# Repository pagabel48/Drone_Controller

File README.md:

# Drone Controller

The control board is based around an STM32f401 MCU. For power regulation a buck converter is used to generate steady 3.3v from a 4s LiPO Battery or USB 5v line. When powered over battery, the highside power latch allows the board to be toggled on or off.

To allow for closed loop control a BMP280 barometer and an ICM42670P IMU are connected over I2C, and PWM is used to communicate with the motor ESCs and controller receiver. Programming is done over USB, and pins are exposed for UART, I2C, and SWD protocols for extensibility.

Four layers were used to make routing easier and improve signal integrity.

## Routing

## Schematic

# Code

State estimation is achieved with two Kalman filters (attitude and altitude), and PID controllers are used in combination with a mixer to get final motor throttle values.

Custom drivers were written to interface with the sensors, and a matrix math library was written using c++ operator overloading - this allows for readable state space control code. The IMU driver reads when triggered by a pin interupt, and the barometer driver uses polling.

A testing routine was written which can be run instead of the main drone loop - it runs unit tests for the code, then tests operation of the sensors, motors, Kalman filters, and status light.

The firmware automatically turns the drone off when the battery voltage drops below a safe level.

Controller Code is Contained in Firmare/Core/

## Code Structure

# Frame

The frame was designed in fusion 360 and was 3d printed using PETG plastic. Care was taken to maximize rigidity whilst minimizing weight.

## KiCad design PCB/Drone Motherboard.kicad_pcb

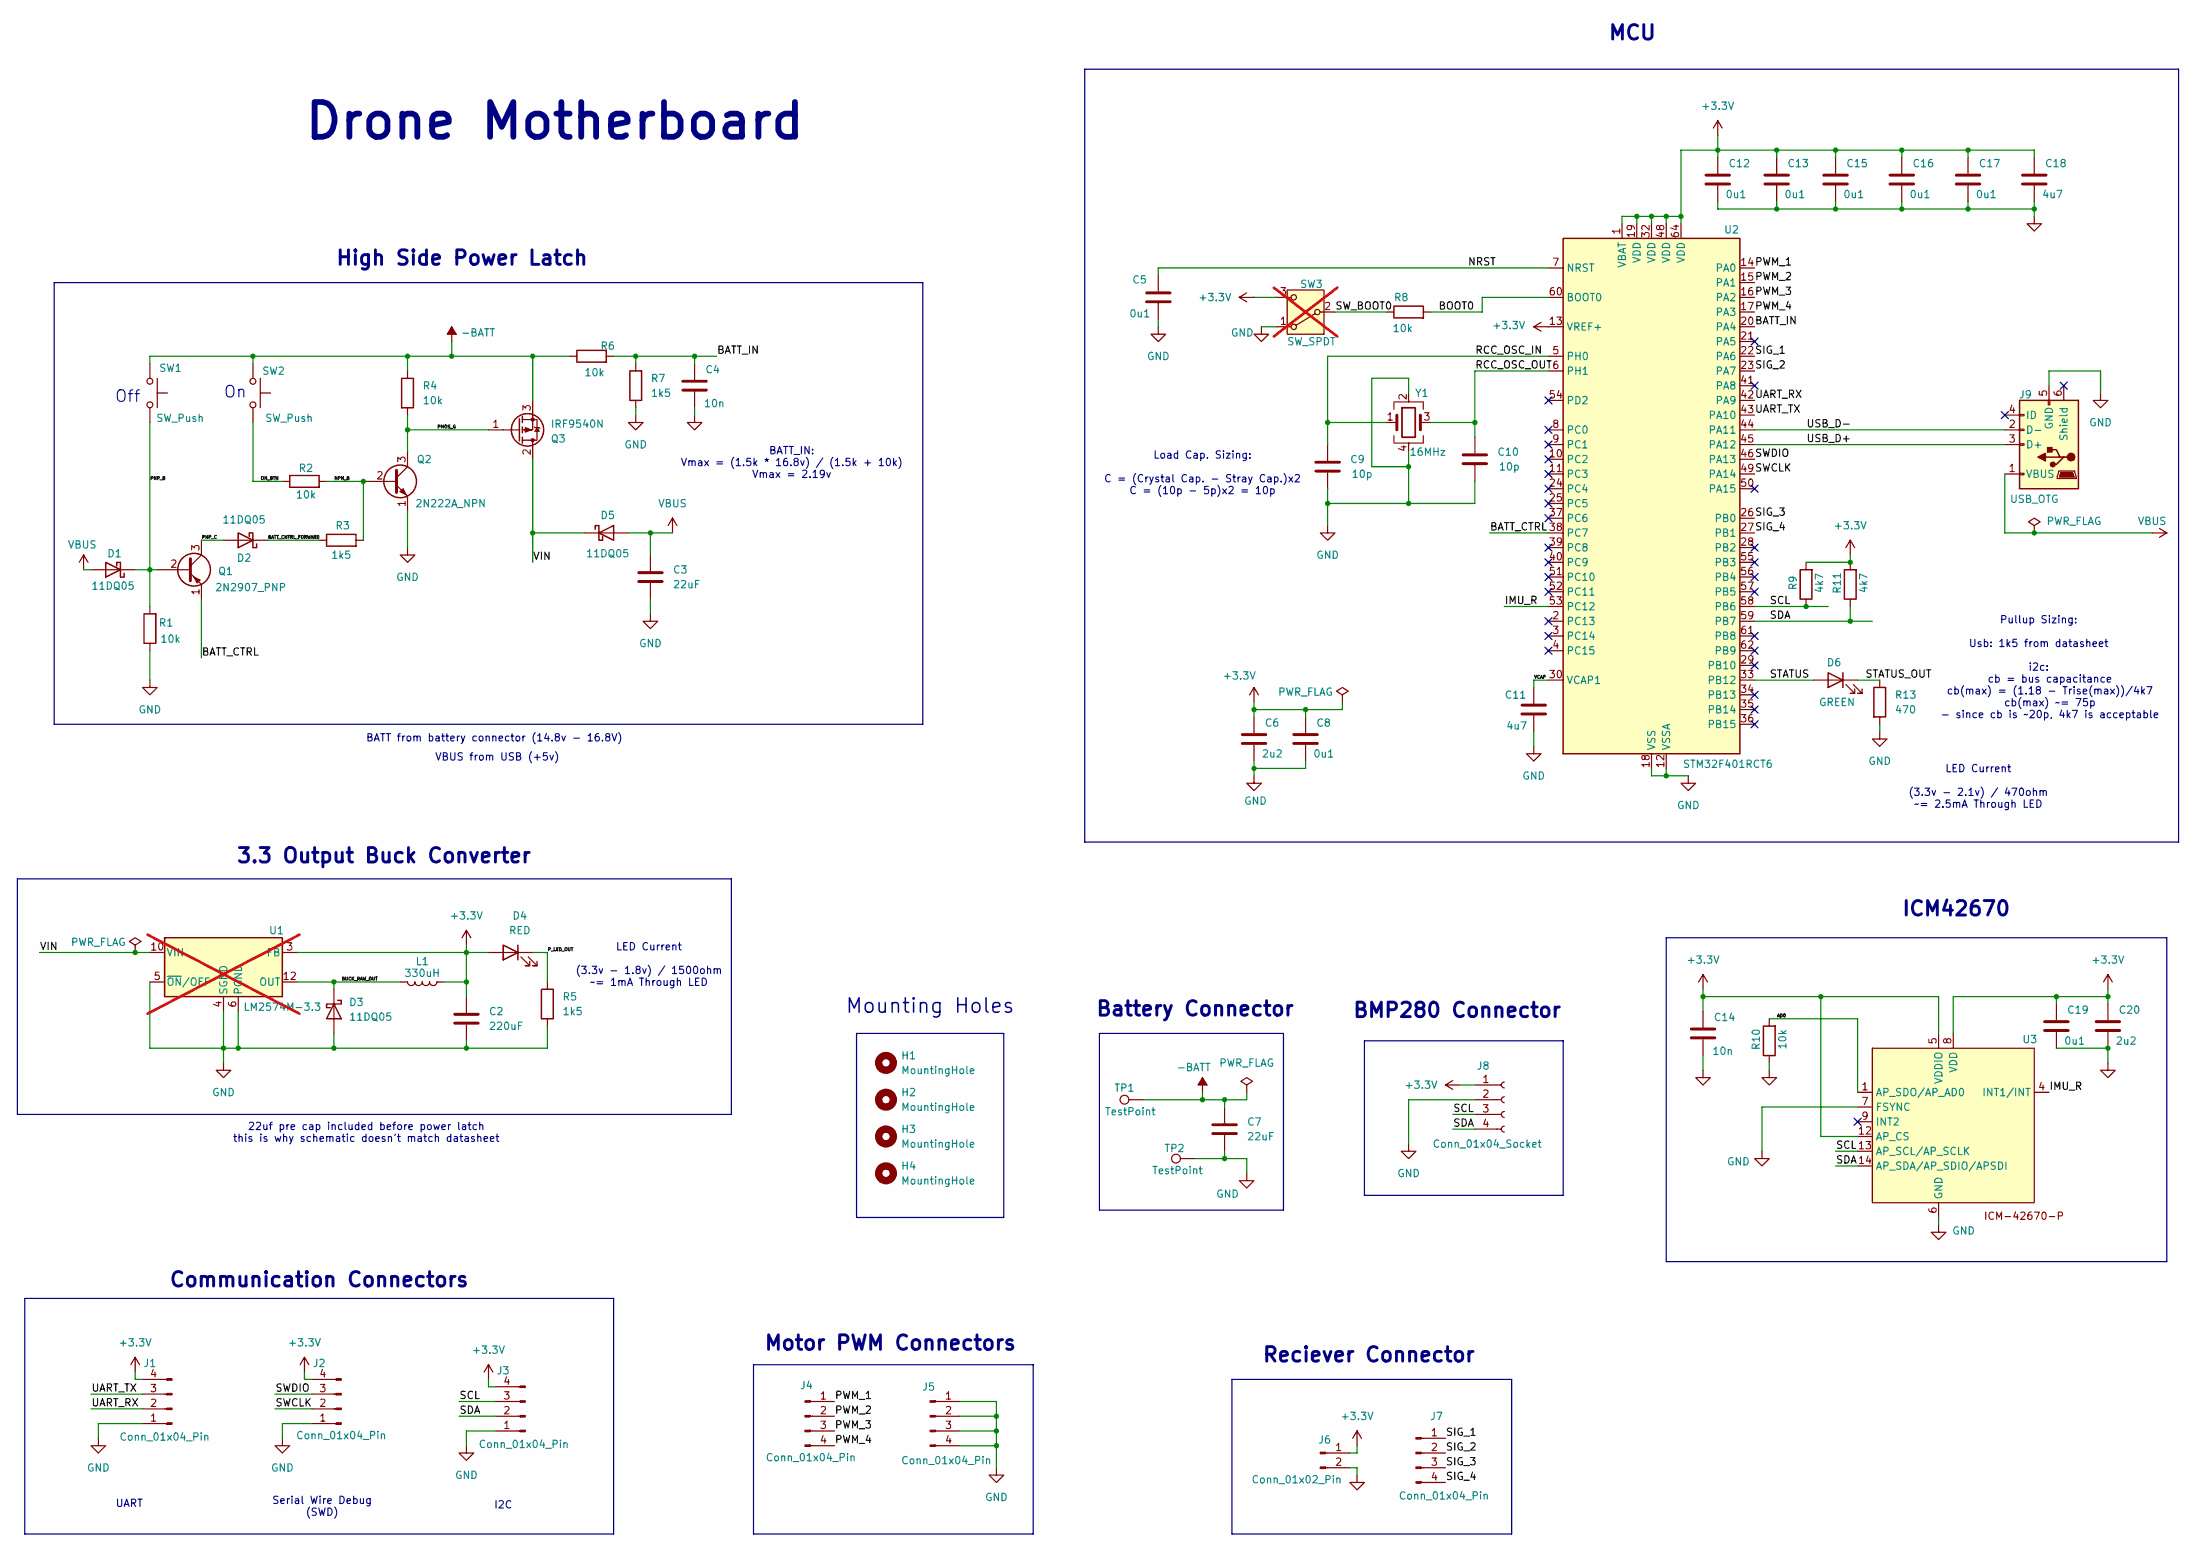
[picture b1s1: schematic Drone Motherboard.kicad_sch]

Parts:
C2: 220uF; C_Radial_D6.3mm_H11.0mm_P2.50mm
C3, C7: 22uF; C_Radial_D5.0mm_H5.0mm_P2.00mm
C4, C14: 10n; C_0402_1005Metric; LCSC C60133
C5, C8, C12, C13, C15, C16, C17, C19: 0u1; C_0402_1005Metric; LCSC C60474
C6, C20: 2u2; C_0402_1005Metric; LCSC C170151
C9, C10: 10p; C_0402_1005Metric; LCSC C106199
C11, C18: 4u7; C_0402_1005Metric; LCSC C23733
D1, D2, D3, D5: 11DQ05; D_DO-41_SOD81_P7.62mm_Horizontal
D4: RED; LED_D5.0mm_Clear
D6: GREEN; LED_D5.0mm_Clear
H1, H2, H3, H4: MountingHole; MountingHole_3.2mm_M3_Pad
J1, J2, J3, J4, J5, J7: Conn_01x04_Pin; PinHeader_1x04_P2.54mm_Vertical
J6: Conn_01x02_Pin; PinHeader_1x02_P2.54mm_Vertical
J8: Conn_01x04_Socket; PinHeader_1x04_P2.54mm_Vertical
J9: USB_OTG; USB_Micro-B_Amphenol_10118193-0001LF_Horizontal; LCSC C132563
L1: 330uH; L_Axial_L5.3mm_D2.2mm_P7.62mm_Horizontal_Vishay_IM-1
Q1: 2N2907_PNP; TO-92
Q2: 2N222A_NPN; TO-92
Q3: IRF9540N; TO-220-3_Vertical
R1, R2, R4, R6, R8, R10: 10k; R_0402_1005Metric; LCSC C25744
R3, R5, R7: 1k5; R_0402_1005Metric; LCSC C25867
R9, R11: 4k7; R_0402_1005Metric; LCSC C105871
R13: 470; R_0402_1005Metric; LCSC C25117
SW1, SW2: SW_Push; SW_PUSH_6mm
SW3: SW_SPDT; CUS-12TB_NDC; not fitted
TP1, TP2: TestPoint; TestPoint_Pad_4.0x4.0mm
U1: LM2574M-3.3; SOIC-14W_7.5x9mm_P1.27mm; not fitted
U2: STM32F401RCT6; LQFP-64_10x10mm_P0.5mm; LCSC C74524
U3: LGA-14_3x2.5mm_P0.5mm_LayoutBorder3x4y; LCSC C3288646
Y1: 16MHz; Crystal_SMD_3225-4Pin_3.2x2.5mm; LCSC C41383241

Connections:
+3.3V: C2.1, C6.1, C8.1, C12.1, C13.1, C14.1, C15.1, C16.1, C17.1, C18.1, C19.1, C20.1, D4.2 (A), J1.4, J2.4, J3.4, J6.1, J8.1, L1.1, R9.2, R11.2, SW3.3 (C), U1.3 (FB), U2.1 (VBAT), U2.13 (VREF+), U2.19 (VDD), U2.32 (VDD), U2.48 (VDD), U2.64 (VDD), U3.5 (VDDIO), U3.8 (VDD), U3.12 (AP_CS)
-BATT: C7.1, Q3.3 (S), R4.1, R6.1, SW1.1, SW2.1, TP1.1
/AD0: R10.2, U3.1 (AP_SDO/AP_AD0)
/BATT_CNTRL_FORWARD: D2.1 (K), R3.1
/BATT_CTRL: Q1.1 (E), U2.38 (PC7)
/BATT_IN: C4.1, R6.2, R7.2, U2.20 (PA4)
/BOOT0: R8.2, U2.60 (BOOT0)
/BUCK_RAW_OUT: D3.1 (K), L1.2, U1.12 (OUT)
/IMU_R: U2.53 (PC12), U3.4 (INT1/INT)
/NPN_B: Q2.2 (B), R2.2, R3.2
/NRST: C5.1, U2.7 (NRST)
/ON_BTN: R2.1, SW2.2
/PMOS_G: Q2.3 (C), Q3.1 (G), R4.2
/PNP_B: D1.1 (K), Q1.2 (B), R1.2, SW1.2
/PNP_C: D2.2 (A), Q1.3 (C)
/PWM_1: J4.1, U2.14 (PA0)
/PWM_2: J4.2, U2.15 (PA1)
/PWM_3: J4.3, U2.16 (PA2)
/PWM_4: J4.4, U2.17 (PA3)
/P_LED_OUT: D4.1 (K), R5.1
/RCC_OSC_IN: C9.1, U2.5 (PH0), Y1.1
/RCC_OSC_OUT: C10.1, U2.6 (PH1), Y1.3
/SCL: J3.3, J8.3, R9.1, U2.58 (PB6), U3.13 (AP_SCL/AP_SCLK)
/SDA: J3.2, J8.4, R11.1, U2.59 (PB7), U3.14 (AP_SDA/AP_SDIO/APSDI)
/SIG_1: J7.1, U2.22 (PA6)
/SIG_2: J7.2, U2.23 (PA7)
/SIG_3: J7.3, U2.26 (PB0)
/SIG_4: J7.4, U2.27 (PB1)
/STATUS: D6.2 (A), U2.33 (PB12)
/STATUS_OUT: D6.1 (K), R13.1
/SWCLK: J2.2, U2.49 (PA14)
/SWDIO: J2.3, U2.46 (PA13)
/SW_BOOT0: R8.1, SW3.2 (B)
/UART_RX: J1.2, U2.42 (PA9)
/UART_TX: J1.3, U2.43 (PA10)
/USB_D+: J9.3 (D+), U2.45 (PA12)
/USB_D-: J9.2 (D-), U2.44 (PA11)
/VCAP: C11.1, U2.30 (VCAP1)
/VIN: D5.1 (K), Q3.2 (D), U1.10 (VIN)
GND: C2.2, C3.2, C4.2, C5.2, C6.2, C7.2, C8.2, C9.2, C10.2, C11.2, C12.2, C13.2, C14.2, C15.2, C16.2, C17.2, C18.2, C19.2, C20.2, D3.2 (A), J1.1, J2.1, J3.1, J5.1, J5.2, J5.3, J5.4, J6.2, J8.2, J9.5 (GND), Q2.1 (E), R1.1, R5.2, R7.1, R10.1, R13.2, SW3.1 (A), TP2.1, U1.4 (SGND), U1.5 (~ON/OFF), U1.6 (PGND), U2.12 (VSSA), U2.18 (VSS), U2.31 (VSS), U2.47 (VSS), U2.63 (VSS), U3.6 (GND), U3.7 (FSYNC), Y1.2, Y1.4
VBUS: C3.1, D1.2 (A), D5.2 (A), J9.1 (VBUS)

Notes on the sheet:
BATT_IN: Vmax = (1.5k * 16.8v) / (1.5k + 10k) Vmax = 2.19v
Serial Wire Debug (SWD)
I2C
Motor PWM Connectors
ICM42670
Drone Motherboard
BATT from battery connector (14.8v - 16.8V)
VBUS from USB (+5v)
High Side Power Latch
3.3 Output Buck Converter
Load Cap. Sizing: C = (Crystal Cap. - Stray Cap.)x2 C = (10p - 5p)x2 = 10p
UART
Off
BMP280 Connector
MCU
LED Current (3.3v - 1.8v) / 1500ohm ~= 1mA Through LED
Pullup Sizing: Usb: 1k5 from datasheet i2c: cb = bus capacitance cb(max) = (1.18 - Trise(max))/4k7 cb(max) ~= 75p - since cb is ~20p, 4k7 is acceptable
22uf pre cap included before power latch this is why schematic doesn't match datasheet
LED Current (3.3v - 2.1v) / 470ohm ~= 2.5mA Through LED
Battery Connector
Communication Connectors
Reciever Connector
Mounting Holes

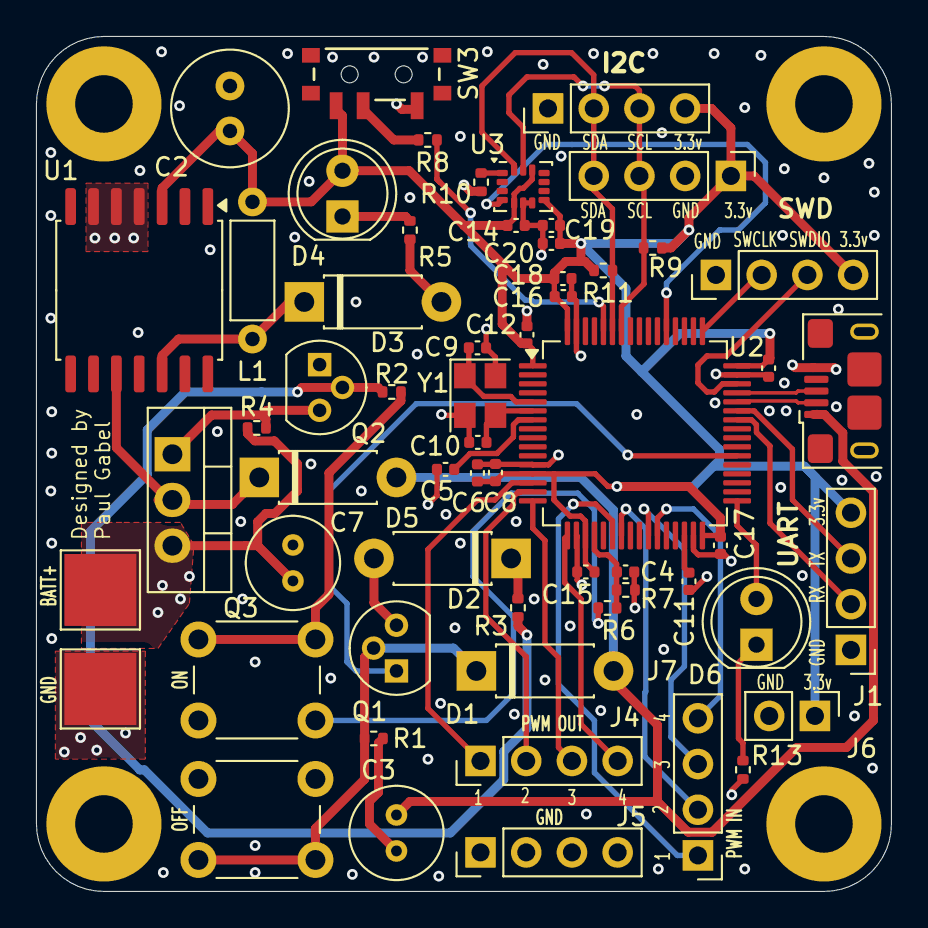
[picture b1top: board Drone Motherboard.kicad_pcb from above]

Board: 4 copper layers, 47.5 x 47.5 mm, 63 parts (0 on the bottom side), 41 nets.

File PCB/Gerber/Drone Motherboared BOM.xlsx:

Designator | Quantity | Description | LCSC Part Number | MPN
TP2,TP1 | 2.0 | TestPoint
Y1 | 1.0 | 16MHz | C41383241
U3 | 1.0 | ICM42670P | C3288646
U2 | 1.0 | STM32F401RCT6 | C74524
U1 | 1.0 | LM2574M-3.3
SW3 | 1.0 | SW_SPDT
SW2,SW1 | 2.0 | SW_Push
R13 | 1.0 | 470.0 | C25117
R11,R9 | 2.0 | 4k7 | C105871
R10,R8,R6,R4,R2,R1 | 6.0 | 10k | C25744
R7,R5,R3 | 3.0 | 1k5 | C25867
Q3 | 1.0 | IRF9540N
Q2 | 1.0 | 2N222A_NPN
Q1 | 1.0 | 2N2907_PNP
L1 | 1.0 | 330uH
J9 | 1.0 | USB_OTG | C132563
J8 | 1.0 | Conn_01x04_Socket
J3,J2,J7,J1,J5,J4 | 6.0 | Conn_01x04_Pin
J6 | 1.0 | Conn_01x02_Pin
D6 | 1.0 | GREEN
D5,D3,D2,D1 | 4.0 | 11DQ05
D4 | 1.0 | RED
C3,C7 | 2.0 | 22uF
C18,C11 | 2.0 | 4u7 | C23733
C17,C19,C16,C15,C13,C12,C8,C5 | 8.0 | 0u1 | C60474
C20,C6 | 2.0 | 2u2 | C170151
C14,C4 | 2.0 | 10n | C60133
C10,C9 | 2.0 | 10p | C106199
C2 | 1.0 | 220uF

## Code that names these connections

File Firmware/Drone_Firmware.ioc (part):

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Mcu.Name=STM32F401R(B-C)Tx
Mcu.Package=LQFP64
Mcu.UserName=STM32F401RCTx
PA0-WKUP.Signal=S_TIM2_CH1_ETR
PA1.Signal=S_TIM2_CH2
PA10.Mode=Asynchronous
PA10.Signal=USART1_RX
PA11.Mode=Device_Only
PA11.Signal=USB_OTG_FS_DM
PA12.Mode=Device_Only
PA12.Signal=USB_OTG_FS_DP
PA13.Mode=Serial_Wire
PA13.Signal=SYS_JTMS-SWDIO
PA14.Mode=Serial_Wire
PA14.Signal=SYS_JTCK-SWCLK
PA2.Signal=S_TIM2_CH3
PA3.Signal=S_TIM2_CH4
PA4.Signal=ADCx_IN4
PA6.Signal=S_TIM3_CH1
PA7.Signal=S_TIM3_CH2
PA9.Mode=Asynchronous
PA9.Signal=USART1_TX
PB0.Signal=S_TIM3_CH3
PB1.Signal=S_TIM3_CH4
PB12.GPIOParameters=GPIO_Label
PB12.GPIO_Label=STATUS
PB12.Signal=GPIO_Output
PB6.Mode=I2C
PB6.Signal=I2C1_SCL
PB7.Mode=I2C
PB7.Signal=I2C1_SDA
PC12.GPIOParameters=GPIO_Label,GPIO_ModeDefaultEXTI
PC12.GPIO_Label=IMU_R
PC12.GPIO_ModeDefaultEXTI=GPIO_MODE_IT_RISING
PC12.Signal=GPXTI12
PC7.GPIOParameters=GPIO_Label
PC7.GPIO_Label=BATT_CTRL
PC7.Signal=GPIO_Output
PH0\ -\ OSC_IN.Mode=HSE-External-Oscillator
PH0\ -\ OSC_IN.Signal=RCC_OSC_IN
PH1\ -\ OSC_OUT.Mode=HSE-External-Oscillator
PH1\ -\ OSC_OUT.Signal=RCC_OSC_OUT
RCC.HSE_VALUE=16000000
RCC.SYSCLKFreq_VALUE=84000000
RCC.SYSCLKSource=RCC_SYSCLKSOURCE_PLLCLK
board=custom

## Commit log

2025-08-26 :star: initial commit
